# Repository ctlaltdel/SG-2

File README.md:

# SG-2 Synthesiser Guitar

## An experimental synth intended to be playable like a guitar

- 2 voices
- A softpot per voice for pitch selection
- A guitar string amplitude detector per voice for volume envelope
- Cartridge port for synth parameter selection

The synth is based around a Daisy Seed from Electrosmith, mounted in a custom PCB that provides the current sources and gating for the softpots, the string amplitude detectors for the voice envelopes, and the cartridge port interface. Power is provided via an internal USB powerbank, charged via a port mounted on the pickguard.

Current status: 
- Revision B of the main electronics board testing complete, awaiting permanent installation
- Port of Op6daisy FM synth engine by @carlvp up and running, including loading synth voice program from cartridge! 

Still to do:
- Add touch-sensitive pads to allow scale shifting up/down to mitigate the limitation of having only 2 strings
- Add a touch control to toggle \'stringless\' playing of the pitch softpots

Here\'s a video that hopefully gives some idea of what I'm aiming at: 

https://www.youtube.com/watch?v=BWaMOtsjMRc

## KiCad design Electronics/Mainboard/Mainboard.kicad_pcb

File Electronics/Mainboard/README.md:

### Credits

- The idea to use constant current to drive the softpots (which allows two-finger hammer-ons and pull-offs) instead of voltage  came from this article:

https://paia.com/dual-ribbon-howto/

- I was having trouble with sound artifacts on finger-off, which was solved with gating based heavily on user frijitz\'s posts on this thread:

https://electro-music.com/forum/topic-32246.html

- The preamp and peak detector of string envelope demodulation stages are based on the Sound Detector product from Sparkfun: 

https://www.sparkfun.com/products/12642

Original schematic by Bryan Jacquot may be found at:

https://cdn.sparkfun.com/assets/8/a/1/2/5/sound-detector-v11.pdf

Note the schematic for this product is released under the Creative Commons
Attribution Share-Alike 3.0 License: https://creativecommons.org/licenses/by-sa/3.0/

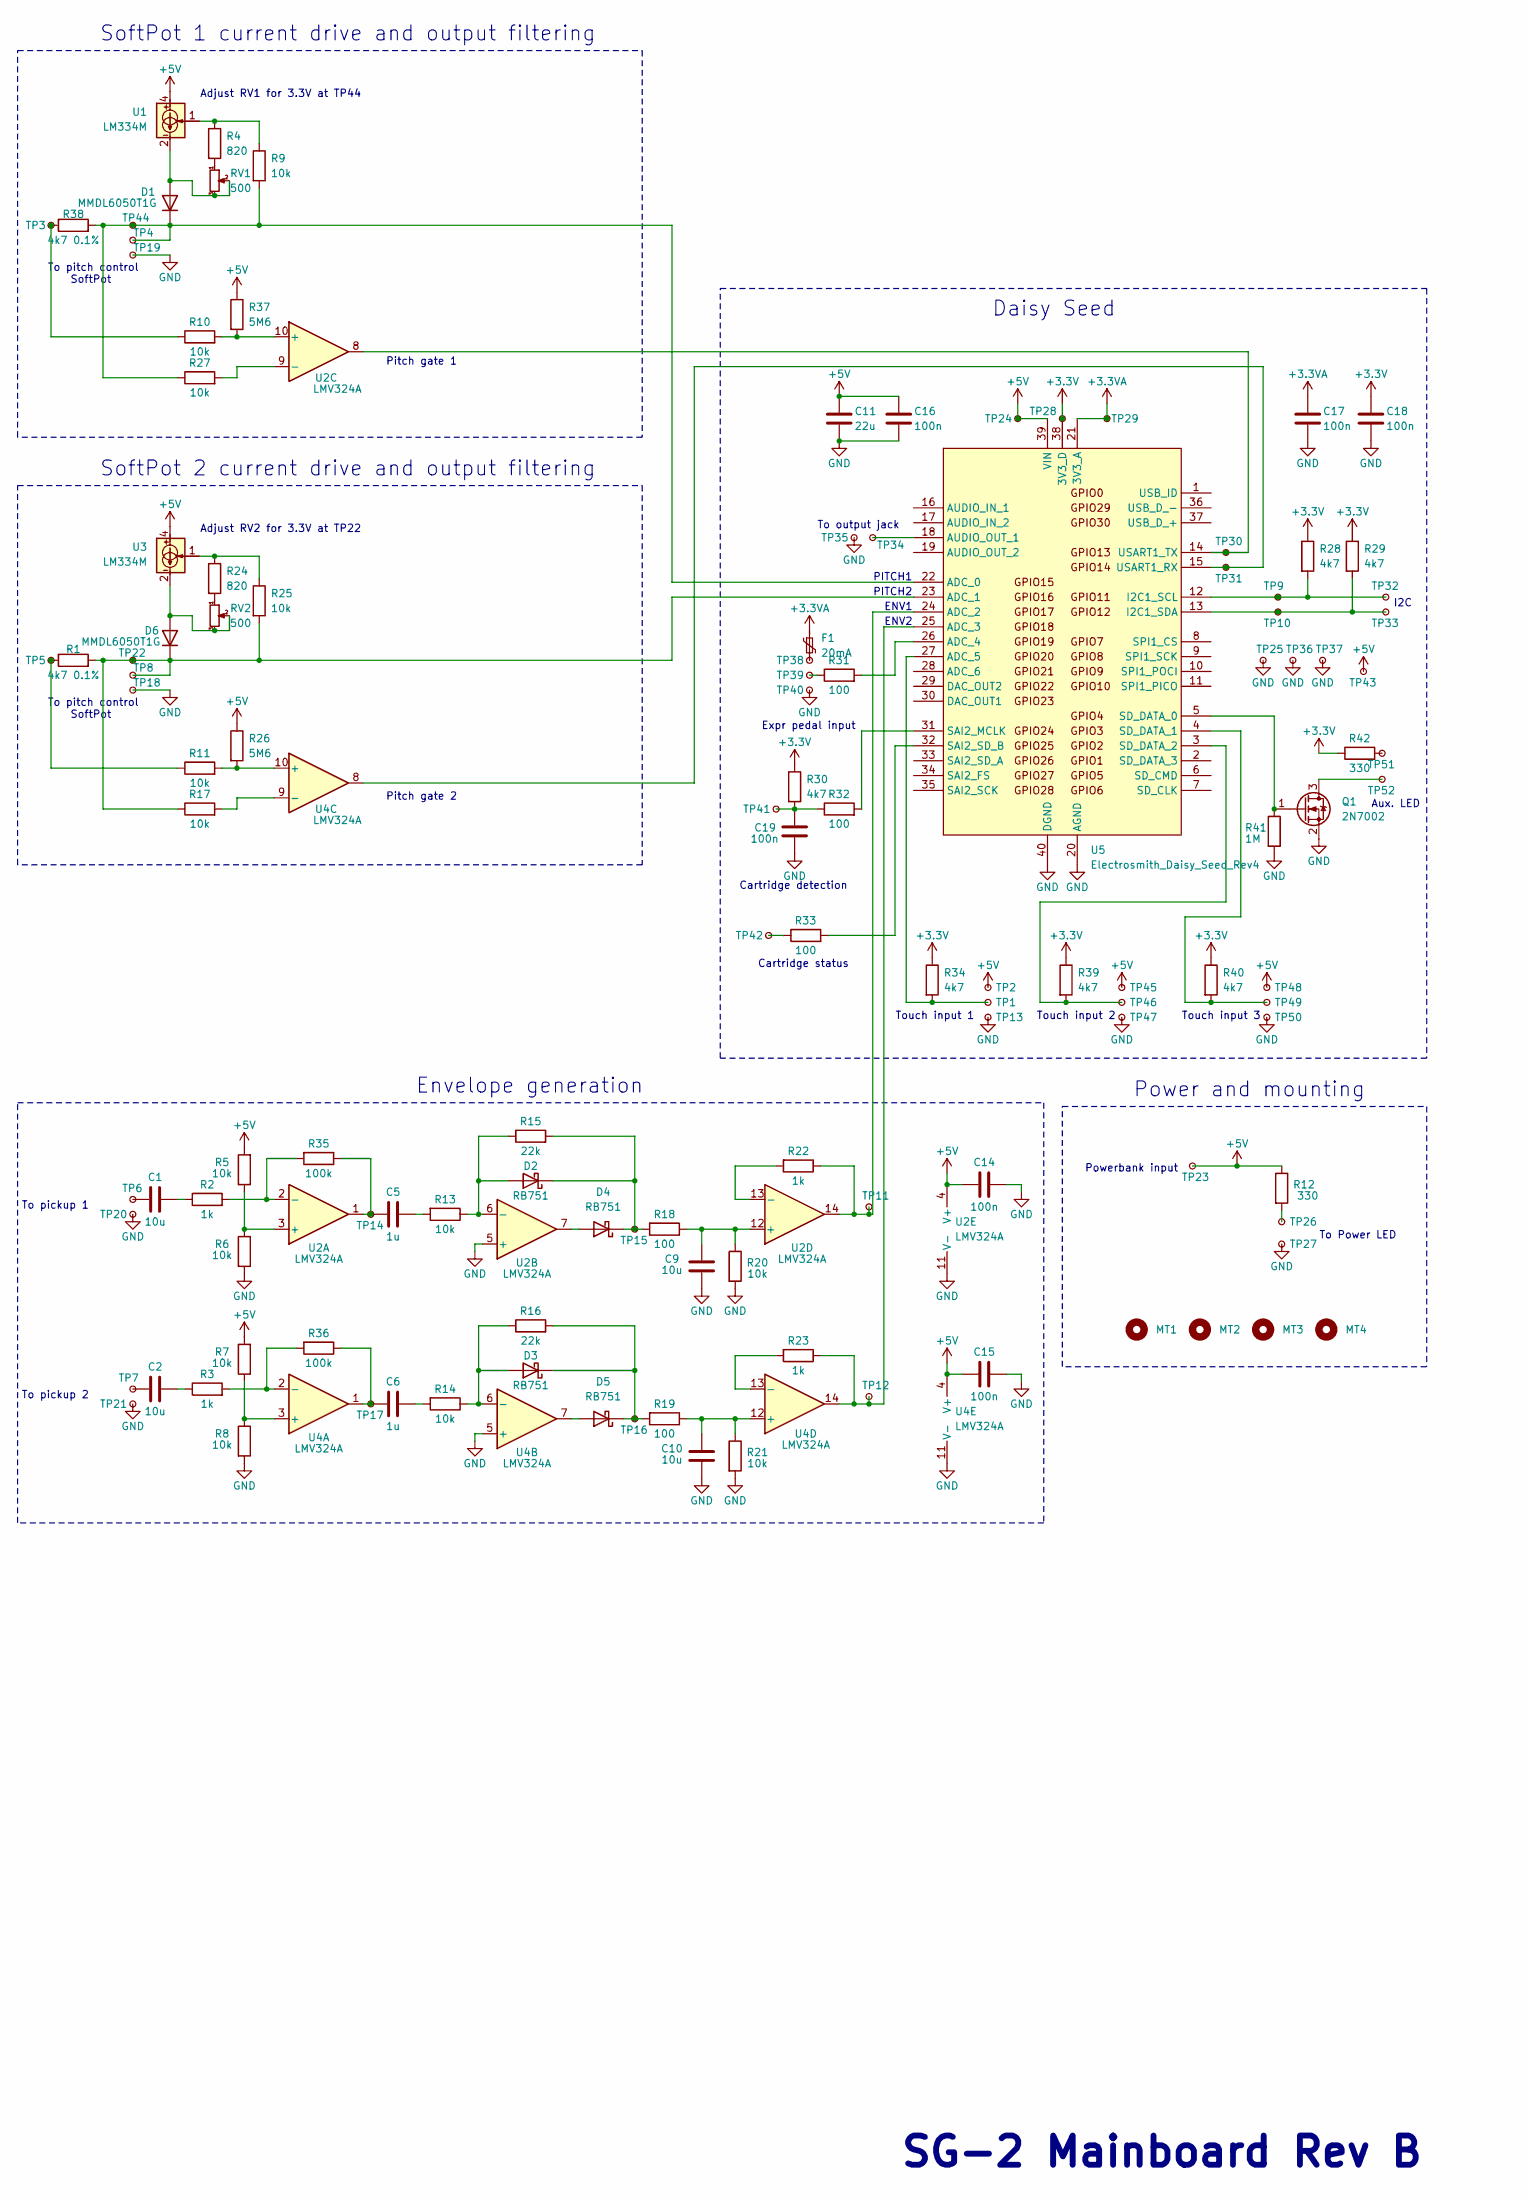
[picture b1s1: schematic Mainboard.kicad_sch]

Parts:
C1, C2, C9, C10: 10u; C_0805_2012Metric
C5, C6: 1u; C_0805_2012Metric
C11: 22u; C_0805_2012Metric
C14, C15, C16, C17, C18, C19: 100n; C_0805_2012Metric
D1, D6: MMDL6050T1G; D_SOD-323
D2, D3, D4, D5: RB751; D_SOD-123F
F1: 20mA; R_0805_2012Metric
MT1, MT2, MT3, MT4: MountingHole; MountingHole_3.2mm_M3
Q1: 2N7002; SOT-23
R1, R38: 4k7 0.1%; R_0805_2012Metric
R2, R3, R22, R23: 1k; R_0805_2012Metric
R4, R24: 820; R_0805_2012Metric
R5, R6, R7, R8, R9, R10, R11, R13, R14, R17, R20, R21, R25, R27: 10k; R_0805_2012Metric
R12, R42: 330; R_0805_2012Metric
R15, R16: 22k; R_0805_2012Metric
R18, R19, R31, R32, R33: 100; R_0805_2012Metric
R26, R37: 5M6; R_0805_2012Metric
R28, R29, R30, R34, R39, R40: 4k7; R_0805_2012Metric
R35, R36: 100k; R_0805_2012Metric
R41: 1M; R_0805_2012Metric
RV1, RV2: 500; Potentiometer_Bourns_3224W_Vertical
TP1, TP2, TP3, TP4, TP5, TP6, TP7, TP8, TP9, TP10, TP11, TP12, TP13, TP14, TP15, TP16, TP17, TP18, TP19, TP20, TP21, TP22, TP23, TP24, TP25, TP26, TP27, TP28, TP29, TP30, TP31, TP32, TP33, TP34, TP35, TP36, TP37, TP38, TP39, TP40, TP41, TP42, TP43, TP44, TP45, TP46, TP47, TP48, TP49, TP50, TP51, TP52: TestPoint_Small; TestPoint_THTPad_D2.0mm_Drill1.0mm
U1, U3: LM334M; SOIC-8_3.9x4.9mm_P1.27mm
U2, U4: LMV324A; SOIC-14_3.9x8.7mm_P1.27mm
U5: Electrosmith_Daisy_Seed_Rev4; Electrosmith_Daisy_Seed

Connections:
+3.3V: C18.2, R28.1, R29.1, R30.1, R34.1, R39.1, R40.1, R42.1, TP28.1, U5.38 (3V3_D)
+3.3VA: C17.2, F1.1, TP29.1, U5.21 (3V3_A)
+5V: C11.2, C14.2, C15.2, C16.2, R5.2, R7.2, R12.1, R26.1, R37.1, TP2.1, TP23.1, TP24.1, TP43.1, TP45.1, TP48.1, U1.4, U2.4 (V+), U3.4, U4.4 (V+), U5.39 (VIN)
GND: C9.2, C10.2, C11.1, C14.1, C15.1, C16.1, C17.1, C18.1, C19.1, Q1.2 (S), R6.2, R8.2, R20.2, R21.2, R41.2, TP13.1, TP18.1, TP19.1, TP20.1, TP21.1, TP25.1, TP27.1, TP35.1, TP36.1, TP37.1, TP40.1, TP47.1, TP50.1, U2.5 (+), U2.11 (V-), U4.5 (+), U4.11 (V-), U5.20 (AGND), U5.40 (DGND)
unnamed: C1.1, R2.1
unnamed: C1.2, TP6.1
unnamed: C2.1, R3.1
unnamed: C2.2, TP7.1
unnamed: C5.1, R13.2
unnamed: C5.2, R35.1, TP14.1, U2.1
unnamed: C6.1, R14.2
unnamed: C6.2, R36.1, TP17.1, U4.1
unnamed: C19.2, R30.2, R32.1, TP41.1
unnamed: D1.2 (A), RV1.2, RV1.3, U1.2, U1.3, U1.6, U1.7
unnamed: D1.1 (K), R9.2, R27.1, R38.2, TP4.1, TP44.1, U5.22 (ADC_0)
unnamed: D2.2 (A), R13.1, R15.1, U2.6 (-)
unnamed: D2.1 (K), D4.1 (K), R15.2, R18.2, TP15.1
unnamed: D3.2 (A), R14.1, R16.1, U4.6 (-)
unnamed: D3.1 (K), D5.1 (K), R16.2, R19.2, TP16.1
unnamed: D4.2 (A), U2.7
unnamed: D5.2 (A), U4.7
unnamed: D6.2 (A), RV2.2, RV2.3, U3.2, U3.3, U3.6, U3.7
unnamed: D6.1 (K), R1.2, R17.1, R25.2, TP8.1, TP22.1, U5.23 (ADC_1)
unnamed: F1.2, TP38.1
unnamed: Q1.3 (D), TP52.1
unnamed: Q1.1 (G), R41.1, U5.5 (SD_DATA_0)
unnamed: R1.1, R11.1, TP5.1
unnamed: R4.1, R9.1, U1.1
unnamed: R4.2, RV1.1
unnamed: R10.1, R38.1, TP3.1
unnamed: R12.2, TP26.1
unnamed: R24.1, R25.1, U3.1
unnamed: R24.2, RV2.1
unnamed: R31.1, TP39.1
unnamed: R33.1, TP42.1
unnamed: R42.2, TP51.1
unnamed: R5.1, R6.1, U2.3 (+)
unnamed: R2.2, R35.2, U2.2 (-)
unnamed: R10.2, R37.2, U2.10 (+)
unnamed: R27.2, U2.9 (-)
unnamed: C9.1, R18.1, R20.1, U2.12 (+)
unnamed: R22.2, U2.13 (-)
unnamed: R7.1, R8.1, U4.3 (+)
unnamed: R3.2, R36.2, U4.2 (-)
unnamed: R11.2, R26.2, U4.10 (+)
unnamed: R17.2, U4.9 (-)
unnamed: C10.1, R19.1, R21.1, U4.12 (+)
unnamed: R23.2, U4.13 (-)
unnamed: R22.1, TP11.1, U2.14, U5.24 (ADC_2)
unnamed: R23.1, TP12.1, U4.14, U5.25 (ADC_3)
unnamed: R31.2, U5.26 (ADC_4)
unnamed: R34.2, TP1.1, U5.27 (ADC_5)
unnamed: TP34.1, U5.18 (AUDIO_OUT_1)
unnamed: R28.2, TP9.1, TP32.1, U5.12 (I2C1_SCL)
unnamed: R29.2, TP10.1, TP33.1, U5.13 (I2C1_SDA)
unnamed: R32.2, U5.31 (SAI2_MCLK)
unnamed: R33.2, U5.32 (SAI2_SD_B)
unnamed: R40.2, TP49.1, U5.4 (SD_DATA_1)
unnamed: R39.2, TP46.1, U5.3 (SD_DATA_2)
unnamed: TP31.1, U4.8, U5.15 (USART1_RX)
unnamed: TP30.1, U2.8, U5.14 (USART1_TX)

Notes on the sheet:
To Power LED
To output jack
Power and mounting
Cartridge status
Powerbank input
Cartridge detection
Pitch gate 1
Envelope generation
SoftPot 2 current drive and output filtering
Touch input 1
ENV2
Aux. LED
Adjust RV1 for 3.3V at TP44
To pitch control SoftPot
I2C
SoftPot 1 current drive and output filtering
Pitch gate 2
PITCH1
Touch input 2
Expr pedal input
To pickup 2
Daisy Seed
To pickup 1
PITCH2
SG-2 Mainboard Rev B
Adjust RV2 for 3.3V at TP22
Touch input 3
ENV1

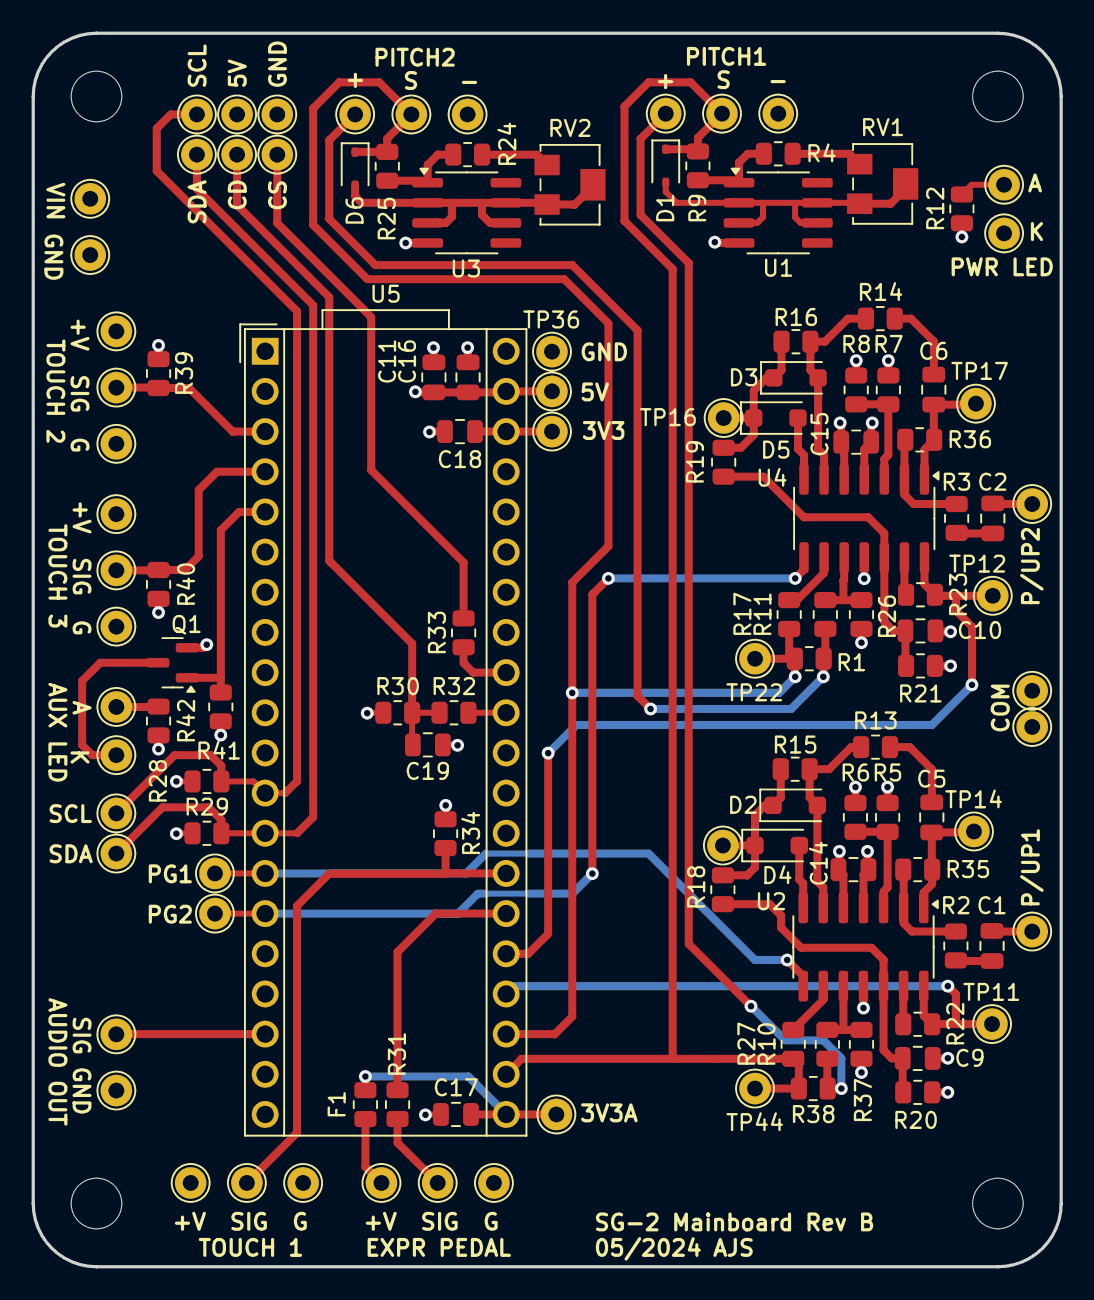
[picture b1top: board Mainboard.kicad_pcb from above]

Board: 4 copper layers, 65.0 x 78.0 mm, 126 parts (0 on the bottom side), 61 nets.

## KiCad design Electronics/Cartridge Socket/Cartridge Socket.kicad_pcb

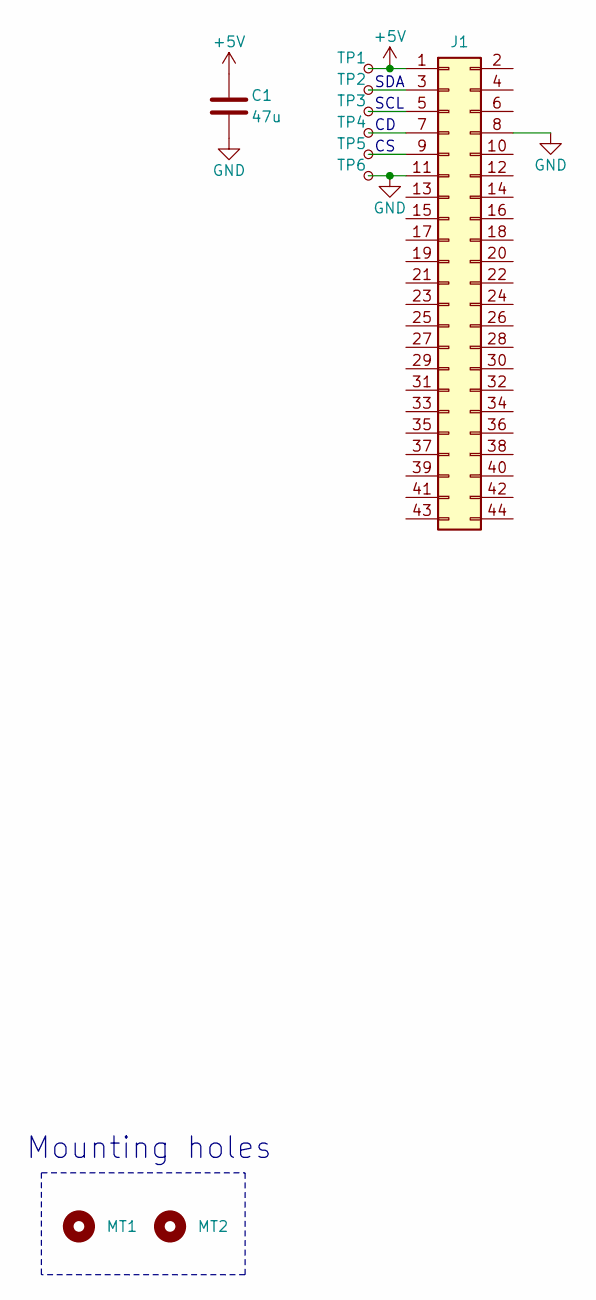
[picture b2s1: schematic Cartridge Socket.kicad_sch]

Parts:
C1: 47u; C_0805_2012Metric
J1: Conn_02x22_Odd_Even; TE_5530843-4
MT1, MT2: MountingHole; MountingHole_3.2mm_M3
TP1, TP2, TP3, TP4, TP5, TP6: TestPoint_Small; TestPoint_THTPad_D1.5mm_Drill0.7mm

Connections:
+5V: C1.2, J1.1, TP1.1
GND: C1.1, J1.8, J1.11, TP6.1
unnamed: J1.3, TP2.1
unnamed: J1.5, TP3.1
unnamed: J1.7, TP4.1
unnamed: J1.9, TP5.1

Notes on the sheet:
SCL
Mounting holes
SDA

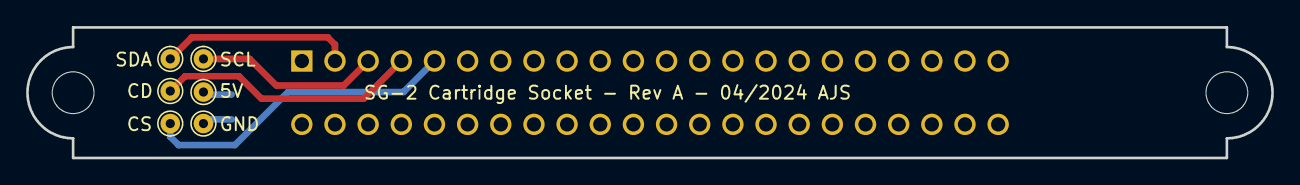
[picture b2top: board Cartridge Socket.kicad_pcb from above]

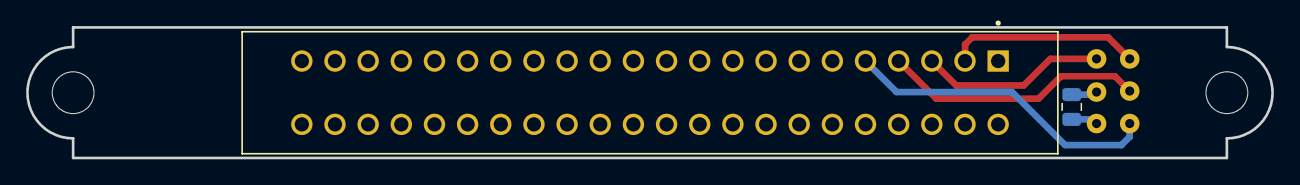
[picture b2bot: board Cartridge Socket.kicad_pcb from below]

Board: 4 copper layers, 95.4 x 10.0 mm, 10 parts (2 on the bottom side), 6 nets.

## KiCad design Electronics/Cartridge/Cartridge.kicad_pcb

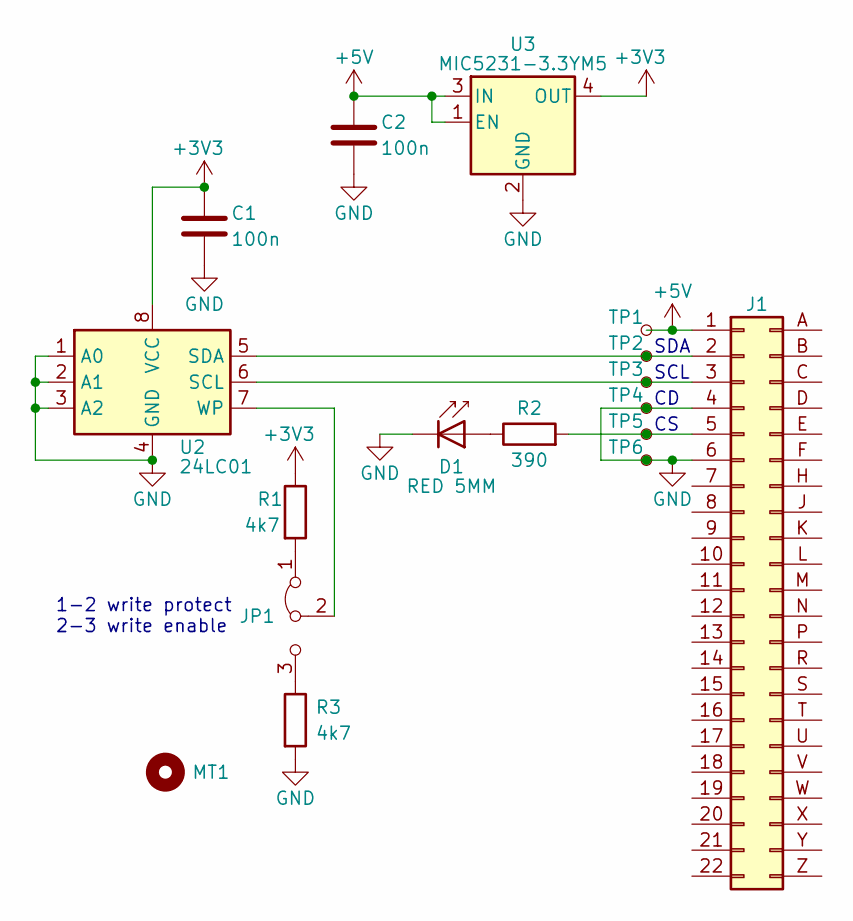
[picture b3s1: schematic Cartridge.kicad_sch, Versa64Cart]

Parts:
C1, C2: 100n; C_0603_1608Metric
D1: RED 5MM; LED_D5.0mm_IRGrey
J1: Conn_02x22_Odd_Even; C64_EXPANSION_PORT
JP1: Jumper_3_Bridged12; PinHeader_1x03_P2.54mm_Horizontal
MT1: MountingHole; MountingHole_5mm
R1, R3: 4k7; R_0805_2012Metric
R2: 390; R_0805_2012Metric
TP1, TP2, TP3, TP4, TP5, TP6: TestPoint_Small; TestPoint_THTPad_D1.5mm_Drill0.7mm
U2: 24LC01; SOIC-8_3.9x4.9mm_P1.27mm
U3: MIC5231-3.3YM5; SOT-23-5

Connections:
+3V3: C1.2, R1.1, U2.8 (VCC), U3.4 (OUT)
+5V: C2.2, J1.1, TP1.1, U3.1 (EN), U3.3 (IN)
GND: C1.1, C2.1, D1.1 (K), J1.4, J1.6, R3.2, TP4.1, TP6.1, U2.1 (A0), U2.2 (A1), U2.3 (A2), U2.4 (GND), U3.2 (GND)
unnamed: D1.2 (A), R2.1
unnamed: J1.5, R2.2, TP5.1
unnamed: JP1.1 (A), R1.2
unnamed: JP1.3 (B), R3.1
unnamed: JP1.2 (C), U2.7 (WP)
unnamed: J1.3, TP3.1, U2.6 (SCL)
unnamed: J1.2, TP2.1, U2.5 (SDA)

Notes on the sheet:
SDA
SCL
1-2 write protect 2-3 write enable

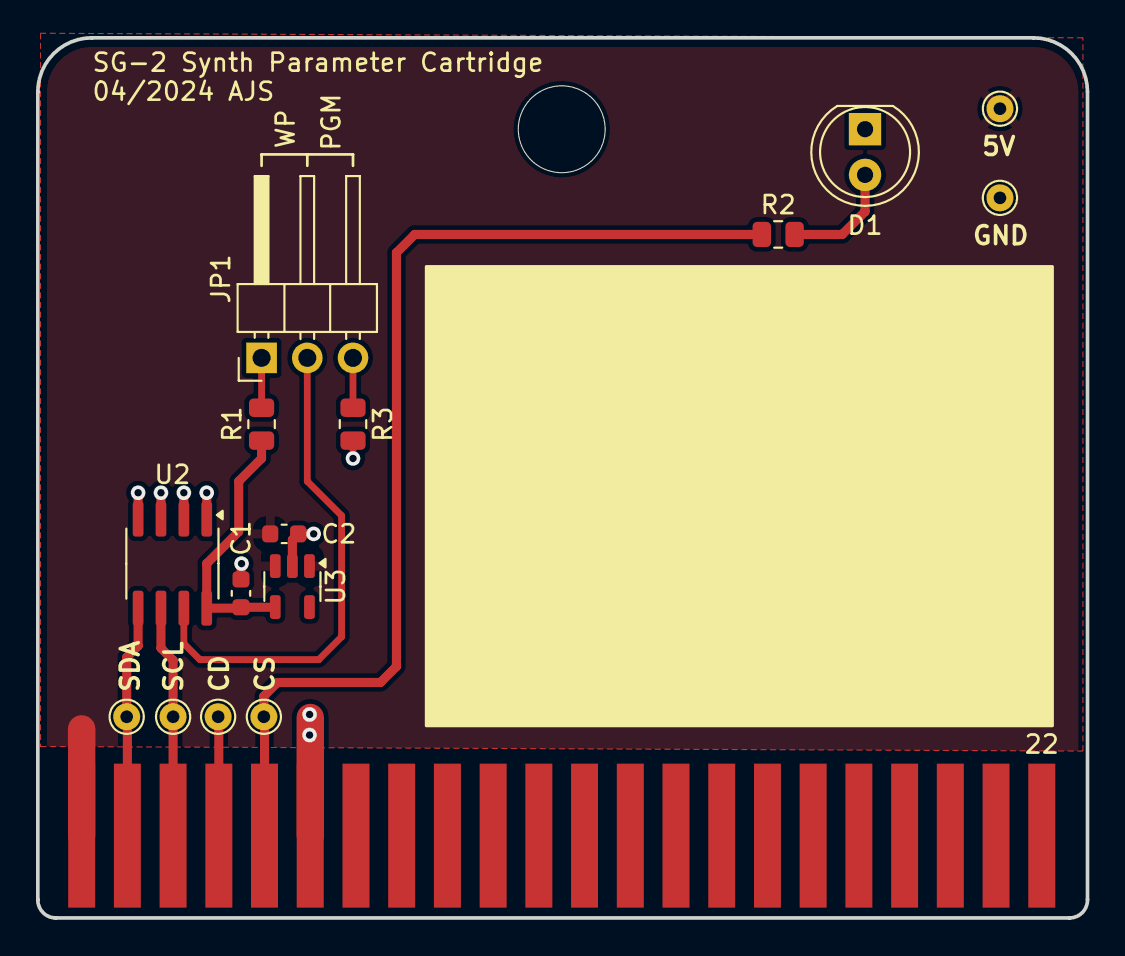
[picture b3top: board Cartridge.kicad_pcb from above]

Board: 2 copper layers, 58.3 x 48.9 mm, 17 parts (0 on the bottom side), 10 nets.

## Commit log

2024-06-01 Did SSH signing work?
2024-06-01 Inital firmware commit
2024-06-03 Added hysteresis to string volume for a clean decay
2024-06-14 Rev B Mainboard and demo firmware
2024-06-17 Added README
2024-06-17 README formatting tweaks
2024-06-17 README minor formatting tweak
2024-06-17 Updates to comply with CC licence 3.0
2024-07-06 Op6daisy port initial commit
2024-07-06 Progress update
2024-07-08 Replace \/ with \_ in patch names
2024-07-08 Replace forward slashes with spaces in patch names
